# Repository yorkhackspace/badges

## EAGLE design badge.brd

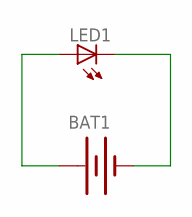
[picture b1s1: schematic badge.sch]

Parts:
BAT1: BATTERY20PTH; BATTCOM_20MM_PTH
LED1: LED5MM
U$1: YHSLOGOFANCY; YHSLOGO_FANCY

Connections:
GND: BAT1.2 (-), LED1.K (C)
unnamed: BAT1.1 (+), LED1.A

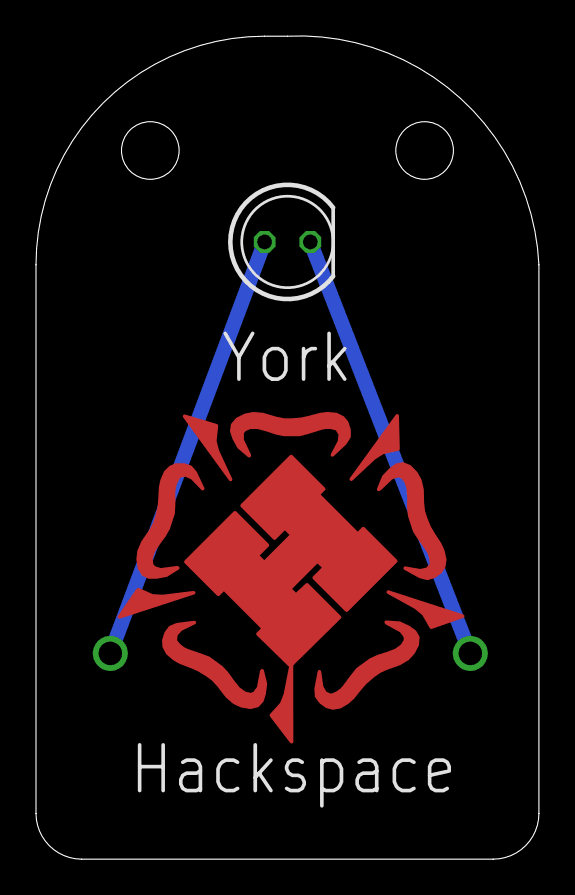
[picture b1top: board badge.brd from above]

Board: 4 copper layers, 27.9 x 45.7 mm, 3 parts (1 on the bottom side), 2 nets.

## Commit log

2014-12-31 Fixed polarity

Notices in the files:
parts and their libraries:
SparkFun-Electromechanical: Licensing: CC v3.0 Share-Alike You are welcome to use this library for commercial purposes.
